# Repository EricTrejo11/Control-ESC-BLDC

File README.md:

View this project on [CADLAB.io](https://cadlab.io/project/30622). 

# Control-ESC-BLDC

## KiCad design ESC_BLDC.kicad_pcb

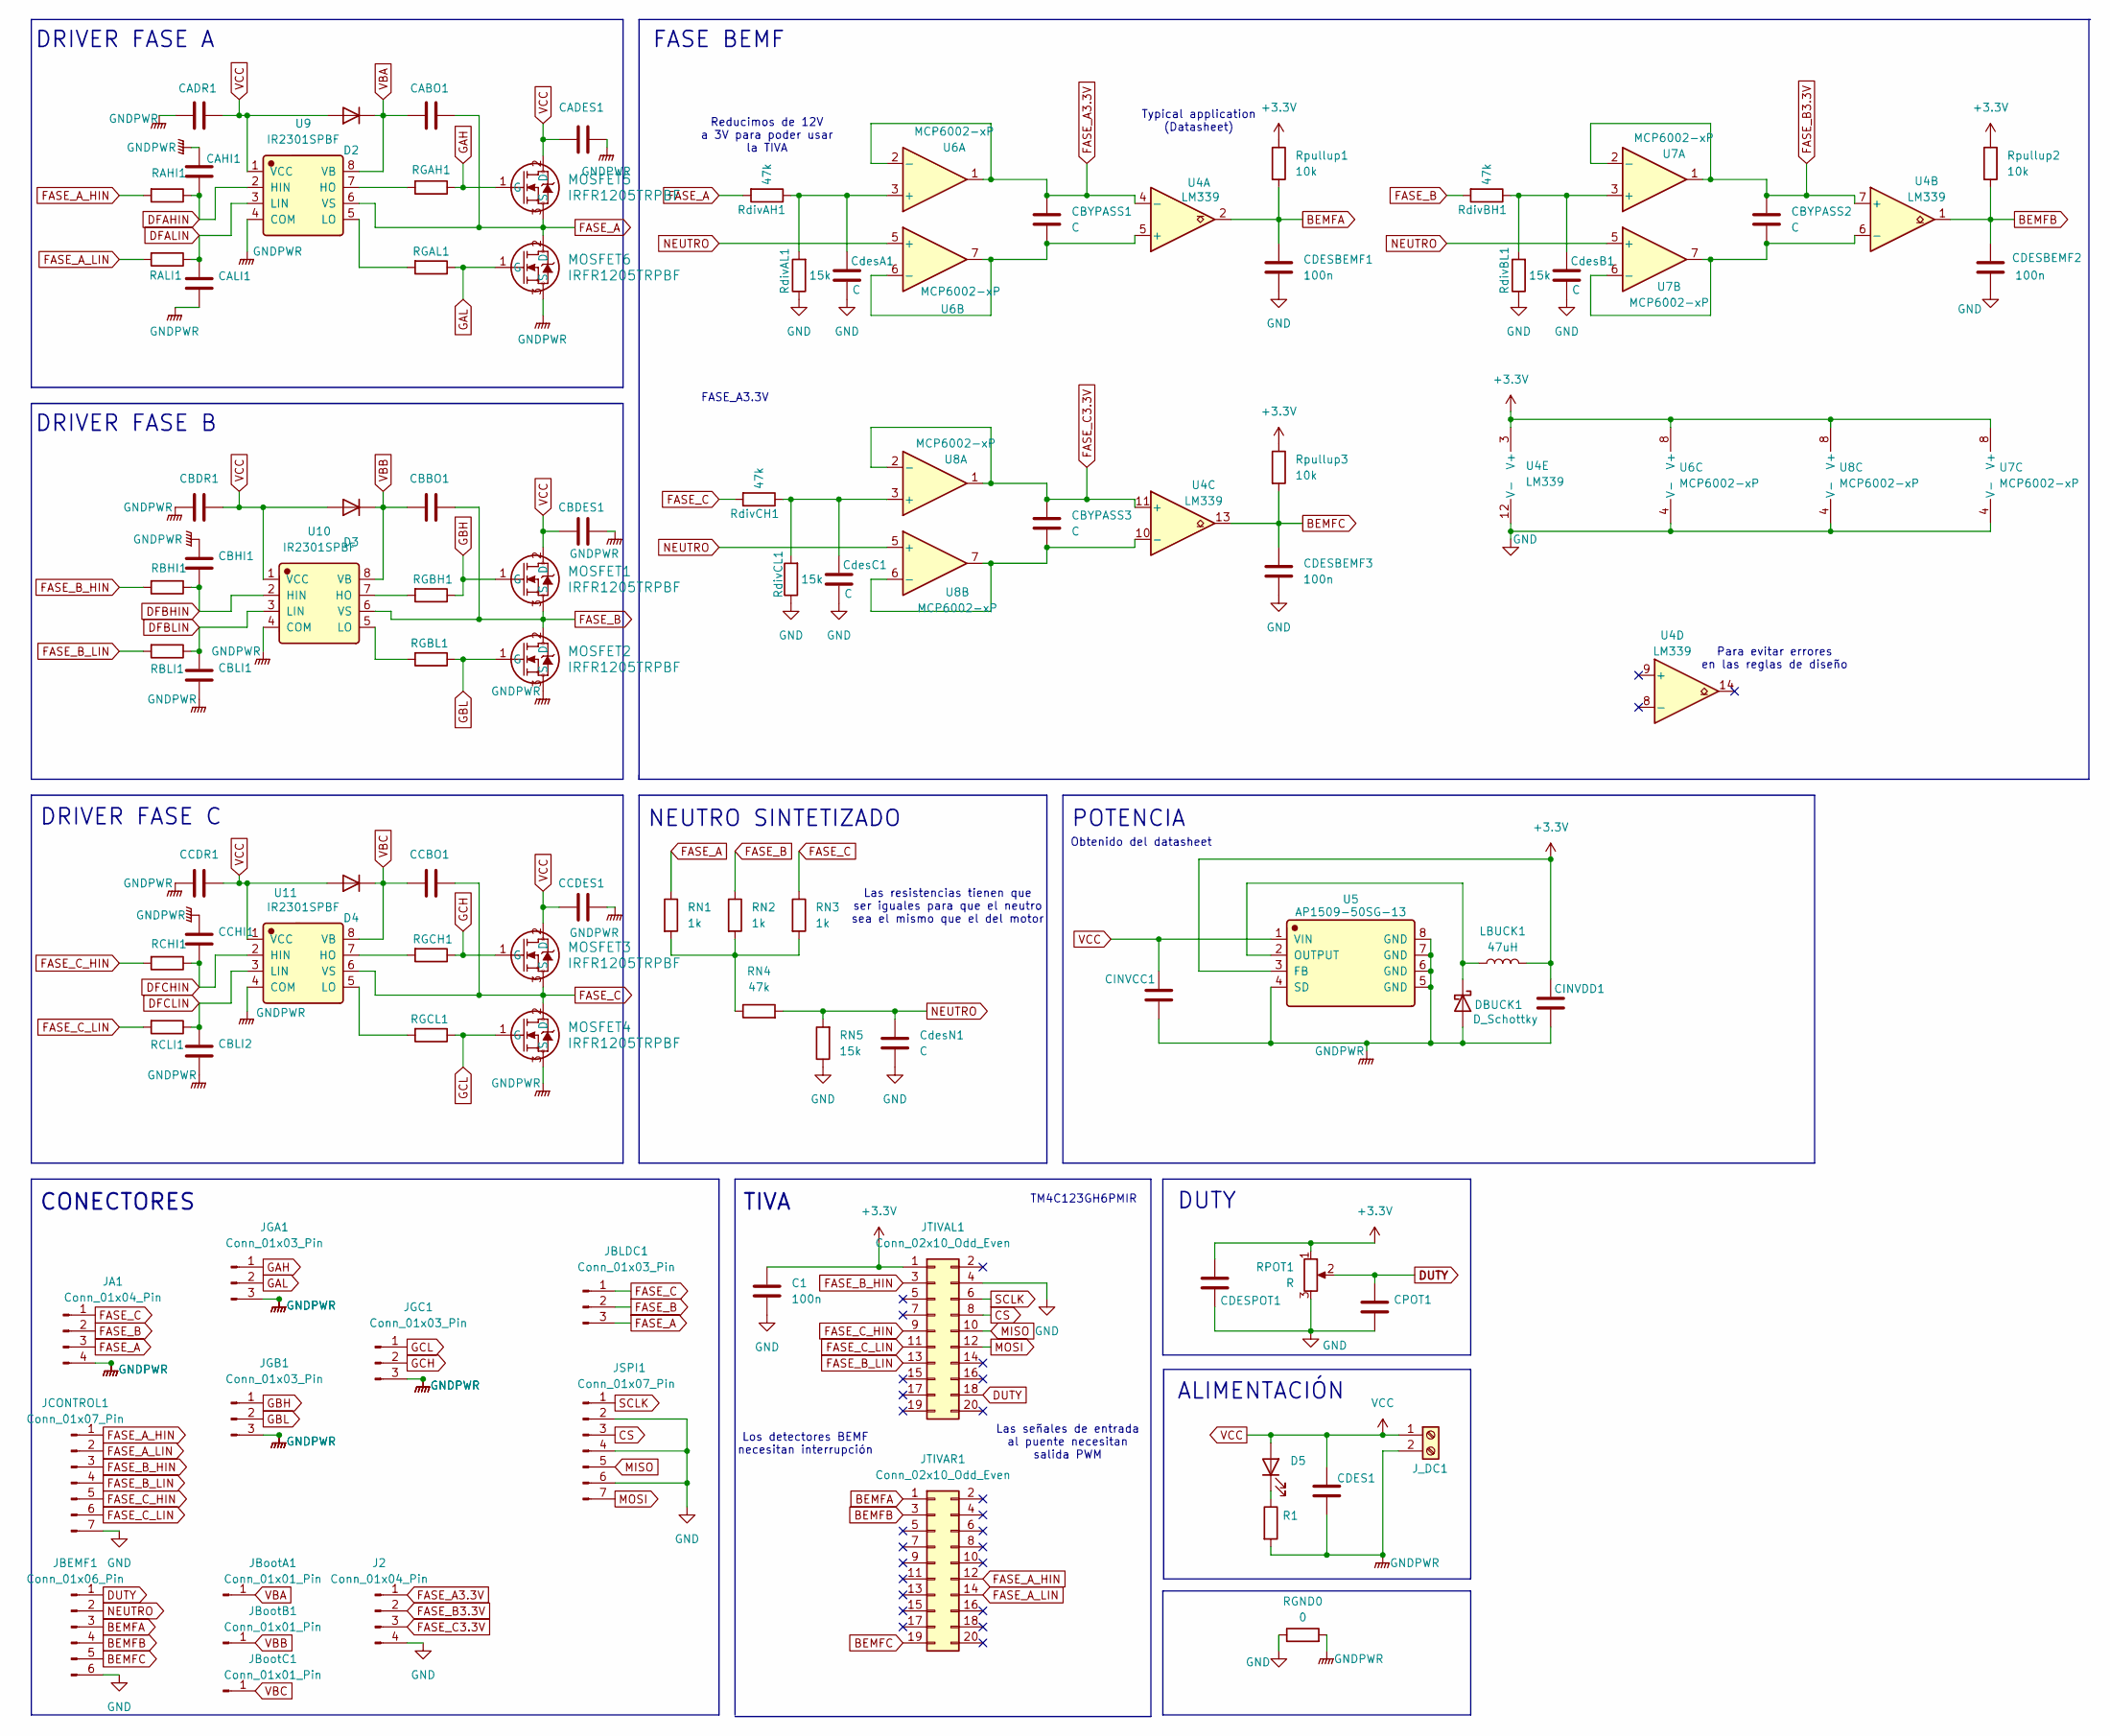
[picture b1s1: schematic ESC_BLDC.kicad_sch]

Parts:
C1: 100n; C_1206_3216Metric_Pad1.33x1.80mm_HandSolder
CABO1: C_1206_3216Metric_Pad1.33x1.80mm_HandSolder
CADES1: C_Elec_6.3x5.8
CADR1: C_1206_3216Metric_Pad1.33x1.80mm_HandSolder
CAHI1: C_1206_3216Metric_Pad1.33x1.80mm_HandSolder
CALI1: C_1206_3216Metric_Pad1.33x1.80mm_HandSolder
CBBO1: C_1206_3216Metric_Pad1.33x1.80mm_HandSolder
CBDES1: C_Elec_6.3x5.8
CBDR1: C_1206_3216Metric_Pad1.33x1.80mm_HandSolder
CBHI1: C_1206_3216Metric_Pad1.33x1.80mm_HandSolder
CBLI1, CBLI2: C_1206_3216Metric_Pad1.33x1.80mm_HandSolder
CBYPASS1, CBYPASS2, CBYPASS3: C; C_1206_3216Metric_Pad1.33x1.80mm_HandSolder
CCBO1: C_1206_3216Metric_Pad1.33x1.80mm_HandSolder
CCDES1: C_Elec_6.3x5.8
CCDR1: C_1206_3216Metric_Pad1.33x1.80mm_HandSolder
CCHI1: C_1206_3216Metric_Pad1.33x1.80mm_HandSolder
CDES1: C_Radial_D12.5mm_H20.0mm_P5.00mm
CDESBEMF1, CDESBEMF2, CDESBEMF3: 100n; C_1206_3216Metric_Pad1.33x1.80mm_HandSolder
CDESPOT1: C_1206_3216Metric_Pad1.33x1.80mm_HandSolder
CINVCC1: C_1206_3216Metric_Pad1.33x1.80mm_HandSolder
CINVDD1: C_1206_3216Metric_Pad1.33x1.80mm_HandSolder
CPOT1: C_1206_3216Metric_Pad1.33x1.80mm_HandSolder
CdesA1: C; C_1206_3216Metric_Pad1.33x1.80mm_HandSolder
CdesB1: C; C_1206_3216Metric_Pad1.33x1.80mm_HandSolder
CdesC1: C; C_1206_3216Metric_Pad1.33x1.80mm_HandSolder
CdesN1: C; C_1206_3216Metric_Pad1.33x1.80mm_HandSolder
D2, D3, D4: D_DO-35_SOD27_P7.62mm_Horizontal
D5: LED_D3.0mm
DBUCK1: D_Schottky; D_DO-34_SOD68_P7.62mm_Horizontal
J2: Conn_01x04_Pin; PinHeader_1x04_P2.54mm_Vertical
JA1: Conn_01x04_Pin; PinHeader_1x04_P2.54mm_Vertical
JBEMF1: Conn_01x06_Pin; PinHeader_1x06_P2.54mm_Vertical
JBLDC1: Conn_01x03_Pin; TerminalBlock_Phoenix_MKDS-1,5-3-5.08_1x03_P5.08mm_Horizont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
JBootA1: Conn_01x01_Pin; PinHeader_1x01_P2.54mm_Vertical
JBootB1: Conn_01x01_Pin; PinHeader_1x01_P2.54mm_Vertical
JBootC1: Conn_01x01_Pin; PinHeader_1x01_P2.54mm_Vertical
JCONTROL1: Conn_01x07_Pin; PinSocket_1x07_P2.54mm_Vertical
JGA1: Conn_01x03_Pin; PinHeader_1x03_P2.54mm_Vertical
JGB1: Conn_01x03_Pin; PinHeader_1x03_P2.54mm_Vertical
JGC1: Conn_01x03_Pin; PinHeader_1x03_P2.54mm_Vertical
JSPI1: Conn_01x07_Pin; PinHeader_1x07_P2.54mm_Vertical
JTIVAL1: Conn_02x10_Odd_Even; PinHeader_2x10_P2.54mm_Vertical
JTIVAR1: Conn_02x10_Odd_Even; PinHeader_2x10_P2.54mm_Vertical
J_DC1: TerminalBlock_Phoenix_MKDS-1,5-2-5.08_1x02_P5.08mm_Horizont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
LBUCK1: 47uH; L_1206_3216Metric_Pad1.42x1.75mm_HandSolder
MOSFET1, MOSFET2, MOSFET3, MOSFET4, MOSFET5, MOSFET6: IRFR1205TRPBF; D-PAK_TO-252AA_INF
R1: R_1206_3216Metric_Pad1.30x1.75mm_HandSolder
RAHI1: R_1206_3216Metric_Pad1.30x1.75mm_HandSolder
RALI1: R_1206_3216Metric_Pad1.30x1.75mm_HandSolder
RBHI1: R_1206_3216Metric_Pad1.30x1.75mm_HandSolder
RBLI1: R_1206_3216Metric_Pad1.30x1.75mm_HandSolder
RCHI1: R_1206_3216Metric_Pad1.30x1.75mm_HandSolder
RCLI1: R_1206_3216Metric_Pad1.30x1.75mm_HandSolder
RGAH1: R_1206_3216Metric_Pad1.30x1.75mm_HandSolder
RGAL1: R_1206_3216Metric_Pad1.30x1.75mm_HandSolder
RGBH1: R_1206_3216Metric_Pad1.30x1.75mm_HandSolder
RGBL1: R_1206_3216Metric_Pad1.30x1.75mm_HandSolder
RGCH1: R_1206_3216Metric_Pad1.30x1.75mm_HandSolder
RGCL1: R_1206_3216Metric_Pad1.30x1.75mm_HandSolder
RGND0: 0; R_1206_3216Metric_Pad1.30x1.75mm_HandSolder
RN1, RN2, RN3: 1k; R_1206_3216Metric_Pad1.30x1.75mm_HandSolder
RN4: 47k; R_1206_3216Metric_Pad1.30x1.75mm_HandSolder
RN5: 15k; R_1206_3216Metric_Pad1.30x1.75mm_HandSolder
RPOT1: R; TerminalBlock_Phoenix_MKDS-1,5-3-5.08_1x03_P5.08mm_Horizont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
RdivAH1: 47k; R_1206_3216Metric_Pad1.30x1.75mm_HandSolder
RdivAL1: 15k; R_1206_3216Metric_Pad1.30x1.75mm_HandSolder
RdivBH1: 47k; R_1206_3216Metric_Pad1.30x1.75mm_HandSolder
RdivBL1: 15k; R_1206_3216Metric_Pad1.30x1.75mm_HandSolder
RdivCH1: 47k; R_1206_3216Metric_Pad1.30x1.75mm_HandSolder
RdivCL1: 15k; R_1206_3216Metric_Pad1.30x1.75mm_HandSolder
Rpullup1, Rpullup2, Rpullup3: 10k; R_1206_3216Metric_Pad1.30x1.75mm_HandSolder
U4: LM339; SOIC-14_3.9x8.7mm_P1.27mm
U5: AP1509-50SG-13; SOP-8_3.9x4.9mm_P1.27mm; Manufacturer Part AP1509-50SG-13; LCSC C9984
U6, U7, U8: MCP6002-xP; SOIC-8_3.9x4.9mm_P1.27mm
U9, U10, U11: IR2301SPBF; SOIC-8_3.9x4.9mm_P1.27mm; Manufacturer Part IR2301SPBF; LCSC C537624

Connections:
+3.3V: C1.1, CDESPOT1.1, CINVDD1.2, JTIVAL1.1, LBUCK1.2, RPOT1.1, Rpullup1.1, Rpullup2.1, Rpullup3.1, U4.3 (V+), U5.3 (FB), U6.8 (V+), U7.8 (V+), U8.8 (V+)
BEMFA: CDESBEMF1.1, JBEMF1.3, JTIVAR1.1, Rpullup1.2, U4.2
BEMFB: CDESBEMF2.1, JBEMF1.4, JTIVAR1.3, Rpullup2.2, U4.1
BEMFC: CDESBEMF3.1, JBEMF1.5, JTIVAR1.19, Rpullup3.2, U4.13
CS: JSPI1.3, JTIVAL1.8
DFAHIN: CAHI1.2, RAHI1.1, U9.2 (HIN)
DFALIN: CALI1.1, RALI1.1, U9.3 (LIN)
DFBHIN: CBHI1.2, RBHI1.1, U10.2 (HIN)
DFBLIN: CBLI1.1, RBLI1.1, U10.3 (LIN)
DFCHIN: CCHI1.2, RCHI1.1, U11.2 (HIN)
DFCLIN: CBLI2.1, RCLI1.1, U11.3 (LIN)
DUTY: CPOT1.1, JBEMF1.1, JTIVAL1.18, RPOT1.2
FASE_A: CABO1.1, JA1.3, JBLDC1.3, MOSFET5.3 (S), MOSFET6.2 (D), RN1.1, RdivAH1.2, U9.6 (VS)
FASE_A3.3V: CBYPASS1.1, J2.1, U4.4 (-), U6.1, U6.2 (-)
FASE_A_HIN: JCONTROL1.1, JTIVAR1.12, RAHI1.2
FASE_A_LIN: JCONTROL1.2, JTIVAR1.14, RALI1.2
FASE_B: CBBO1.1, JA1.2, JBLDC1.2, MOSFET1.3 (S), MOSFET2.2 (D), RN2.1, RdivBH1.2, U10.6 (VS)
FASE_B3.3V: CBYPASS2.1, J2.2, U4.7 (+), U7.1, U7.2 (-)
FASE_B_HIN: JCONTROL1.3, JTIVAL1.3, RBHI1.2
FASE_B_LIN: JCONTROL1.4, JTIVAL1.13, RBLI1.2
FASE_C: CCBO1.1, JA1.1, JBLDC1.1, MOSFET3.3 (S), MOSFET4.2 (D), RN3.1, RdivCH1.2, U11.6 (VS)
FASE_C3.3V: CBYPASS3.1, J2.3, U4.11 (+), U8.1, U8.2 (-)
FASE_C_HIN: JCONTROL1.5, JTIVAL1.9, RCHI1.2
FASE_C_LIN: JCONTROL1.6, JTIVAL1.11, RCLI1.2
GAH: JGA1.1, MOSFET5.1 (G), RGAH1.1
GAL: JGA1.2, MOSFET6.1 (G), RGAL1.1
GBH: JGB1.1, MOSFET1.1 (G), RGBH1.1
GBL: JGB1.2, MOSFET2.1 (G), RGBL1.1
GCH: JGC1.2, MOSFET3.1 (G), RGCH1.1
GCL: JGC1.1, MOSFET4.1 (G), RGCL1.1
GND: C1.2, CDESBEMF1.2, CDESBEMF2.2, CDESBEMF3.2, CDESPOT1.2, CPOT1.2, CdesA1.2, CdesB1.2, CdesC1.2, CdesN1.2, J2.4, JBEMF1.6, JCONTROL1.7, JSPI1.2, JSPI1.4, JSPI1.6, JTIVAL1.4, RGND0.1, RN5.1, RPOT1.3, RdivAL1.1, RdivBL1.1, RdivCL1.1, U4.12 (V-), U6.4 (V-), U7.4 (V-), U8.4 (V-)
GNDPWR: CADES1.1, CADR1.2, CAHI1.1, CALI1.2, CBDES1.1, CBDR1.2, CBHI1.1, CBLI1.2, CBLI2.2, CCDES1.1, CCDR1.2, CCHI1.1, CDES1.2, CINVCC1.2, CINVDD1.1, DBUCK1.2 (A), JA1.4, JGA1.3, JGB1.3, JGC1.3, J_DC1.2, MOSFET2.3 (S), MOSFET4.3 (S), MOSFET6.3 (S), R1.2, RGND0.2, U5.4 (SD), U5.5 (GND), U5.6 (GND), U5.7 (GND), U5.8 (GND), U9.4 (COM), U10.4 (COM), U11.4 (COM)
MISO: JSPI1.5, JTIVAL1.10
MOSI: JSPI1.7, JTIVAL1.12
NEUTRO: CdesN1.1, JBEMF1.2, RN4.2, RN5.2, U6.5 (+), U7.5 (+), U8.5 (+)
unnamed: D5.1 (K), R1.1
unnamed: DBUCK1.1 (K), LBUCK1.1, U5.2 (OUTPUT)
unnamed: RN1.2, RN2.2, RN3.2, RN4.1
unnamed: CBYPASS1.2, U4.5 (+), U6.6 (-), U6.7
unnamed: CBYPASS2.2, U4.6 (-), U7.6 (-), U7.7
unnamed: CBYPASS3.2, U4.10 (-), U8.6 (-), U8.7
unnamed: CdesA1.1, RdivAH1.1, RdivAL1.2, U6.3 (+)
unnamed: CdesB1.1, RdivBH1.1, RdivBL1.2, U7.3 (+)
unnamed: CdesC1.1, RdivCH1.1, RdivCL1.2, U8.3 (+)
unnamed: RGAH1.2, U9.7 (HO)
unnamed: RGAL1.2, U9.5 (LO)
unnamed: RGBH1.2, U10.7 (HO)
unnamed: RGBL1.2, U10.5 (LO)
unnamed: RGCH1.2, U11.7 (HO)
unnamed: RGCL1.2, U11.5 (LO)
SCLK: JSPI1.1, JTIVAL1.6
VBA: CABO1.2, D2.1 (K), JBootA1.1, U9.8 (VB)
VBB: CBBO1.2, D3.1 (K), JBootB1.1, U10.8 (VB)
VBC: CCBO1.2, D4.1 (K), JBootC1.1, U11.8 (VB)
VCC: CADES1.2, CADR1.1, CBDES1.2, CBDR1.1, CCDES1.2, CCDR1.1, CDES1.1, CINVCC1.1, D2.2 (A), D3.2 (A), D4.2 (A), D5.2 (A), J_DC1.1, MOSFET1.2 (D), MOSFET3.2 (D), MOSFET5.2 (D), U5.1 (VIN), U9.1 (VCC), U10.1 (VCC), U11.1 (VCC)

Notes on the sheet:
ALIMENTACIÓN
POTENCIA
DRIVER FASE B
Typical application (Datasheet)
TM4C123GH6PMIR
Reducimos de 12V a 3V para poder usar la TIVA
Para evitar errores en las reglas de diseño
Los detectores BEMF necesitan interrupción
Las señales de entrada al puente necesitan salida PWM
DUTY
FASE_A3.3V
Obtenido del datasheet
TIVA
Las resistencias tienen que ser iguales para que el neutro sea el mismo que el del motor
CONECTORES
FASE BEMF
NEUTRO SINTETIZADO
DRIVER FASE C
DRIVER FASE A

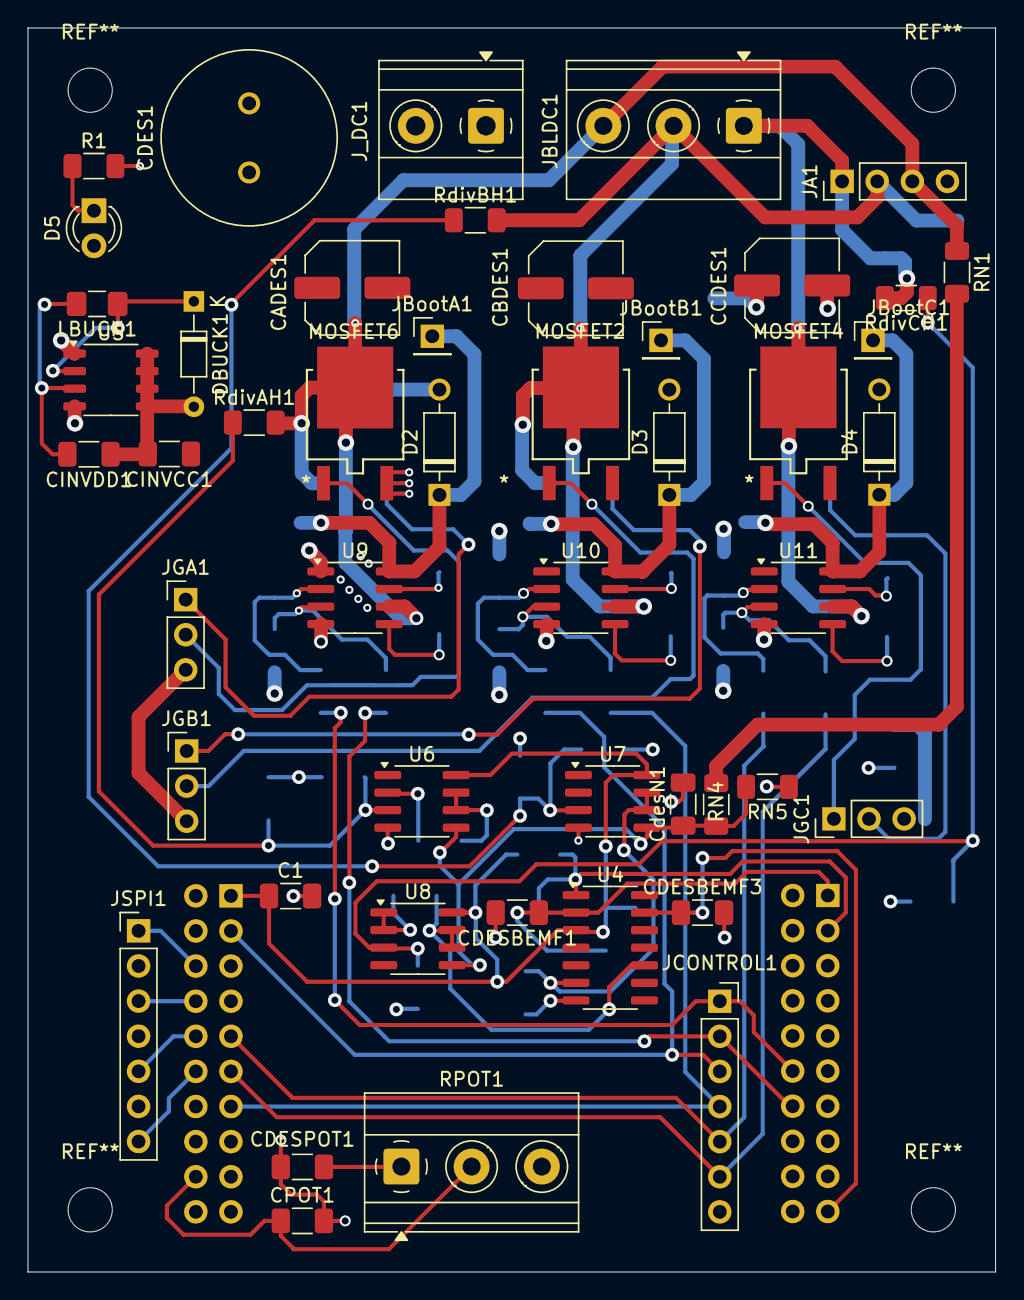
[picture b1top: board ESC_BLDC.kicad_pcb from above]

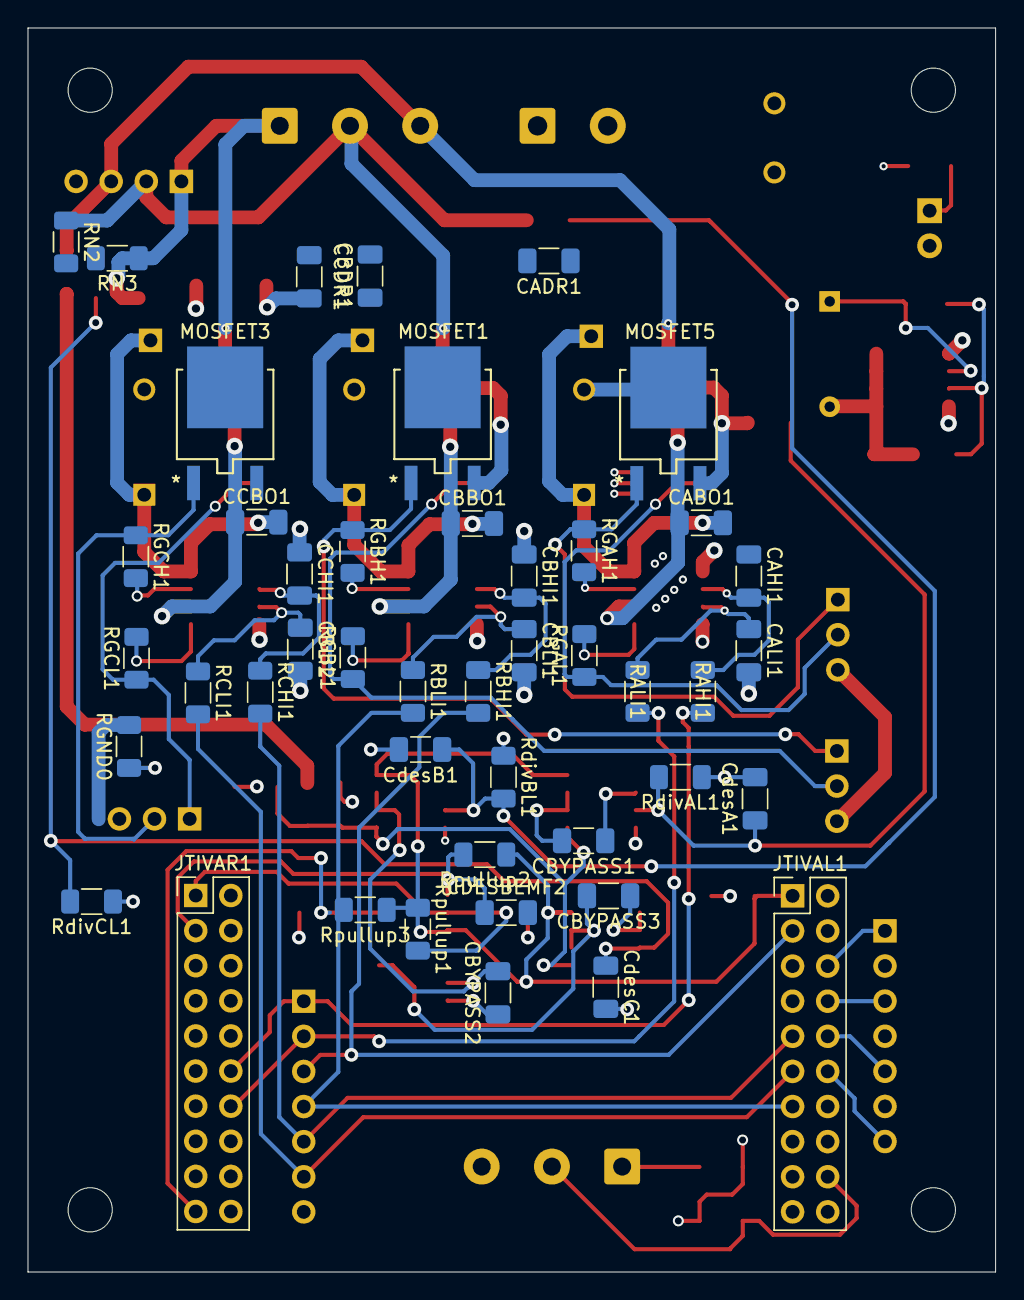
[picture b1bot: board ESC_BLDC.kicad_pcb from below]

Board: 4 copper layers, 70.0 x 90.0 mm, 93 parts (45 on the bottom side), 55 nets.
